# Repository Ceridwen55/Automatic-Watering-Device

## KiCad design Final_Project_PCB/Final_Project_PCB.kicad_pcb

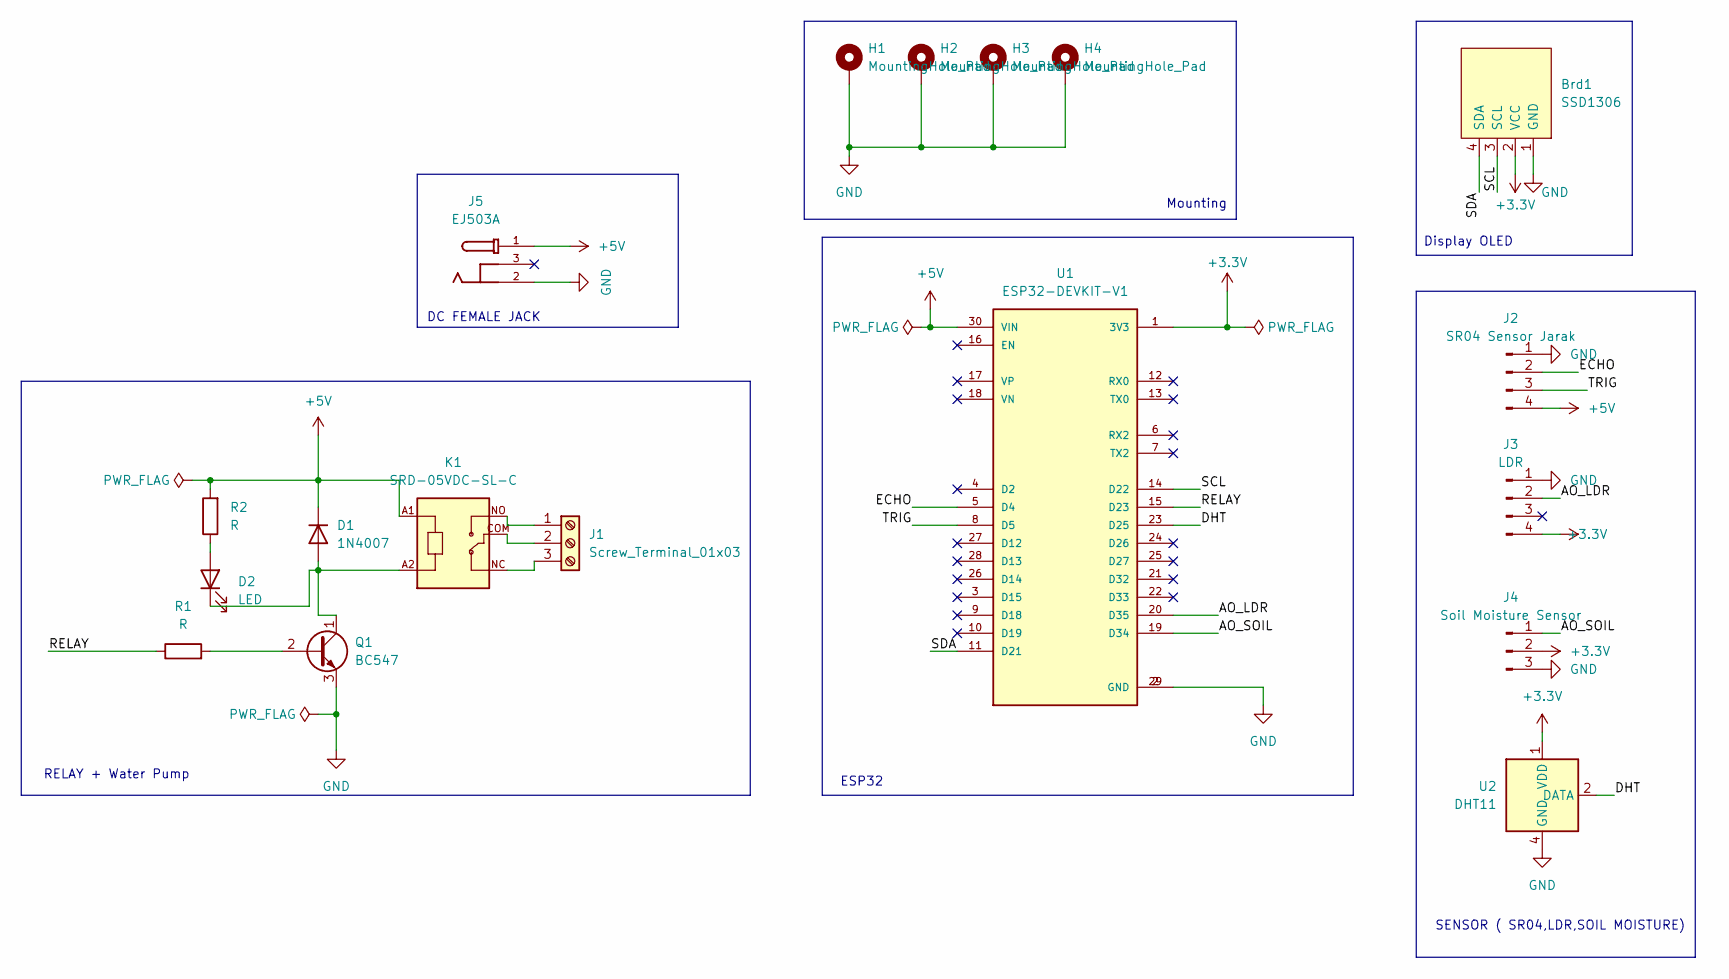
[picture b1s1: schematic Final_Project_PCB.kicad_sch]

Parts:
Brd1: SSD1306; 128x64OLED
D1: 1N4007; D_DO-41_SOD81_P10.16mm_Horizontal
D2: LED; LED_D3.0mm
H1, H2, H3, H4: MountingHole_Pad; MountingHole_3.2mm_M3_ISO14580_Pad
J1: Screw_Terminal_01x03; TerminalBlock_Phoenix_MKDS-1,5-3-5.08_1x03_P5.08mm_Horizont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
J2: SR04 Sensor Jarak; PinHeader_1x04_P2.54mm_Vertical
J3: LDR; PinHeader_1x04_P2.54mm_Vertical
J4: Soil Moisture Sensor; PinHeader_1x03_P2.54mm_Vertical
J5: EJ503A; MPD_EJ503A; PARTREV B
K1: SRD-05VDC-SL-C; RELAY_SRD-05VDC-SL-C
Q1: BC547; TO-92_Inline
R1, R2: R; R_Axial_DIN0207_L6.3mm_D2.5mm_P10.16mm_Horizontal
U1: ESP32-DEVKIT-V1; MODULE_ESP32_DEVKIT_V1; PARTREV N/A
U2: DHT11; Aosong_DHT11_5.5x12.0_P2.54mm

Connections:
+3.3V: Brd1.2 (VCC), J3.4, J4.2, U1.1 (3V3), U2.1 (VDD)
+5V: D1.1 (K), J2.4, J5.1, K1.A1, R2.2, U1.30 (VIN)
/AO_LDR: J3.2, U1.20 (D35)
/AO_SOIL: J4.1, U1.19 (D34)
/DHT: U1.23 (D25), U2.2 (DATA)
/ECHO: J2.2, U1.5 (D4)
/RELAY: R1.1, U1.15 (D23)
/SCL: Brd1.3 (SCL), U1.14 (D22)
/SDA: Brd1.4 (SDA), U1.11 (D21)
/TRIG: J2.3, U1.8 (D5)
GND: Brd1.1 (GND), H1.1, H2.1, H3.1, H4.1, J2.1, J3.1, J4.3, J5.2, Q1.3 (E), U1.2 (GND), U1.29 (GND), U2.4 (GND)
unnamed: D1.2 (A), D2.1 (K), K1.A2, Q1.1 (C)
unnamed: D2.2 (A), R2.1
unnamed: J1.1, K1.NO
unnamed: J1.2, K1.COM
unnamed: J1.3, K1.NC
unnamed: Q1.2 (B), R1.2

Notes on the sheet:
SENSOR ( SR04,LDR,SOIL MOISTURE)
Display OLED
Mounting
DC FEMALE JACK
RELAY + Water Pump
ESP32

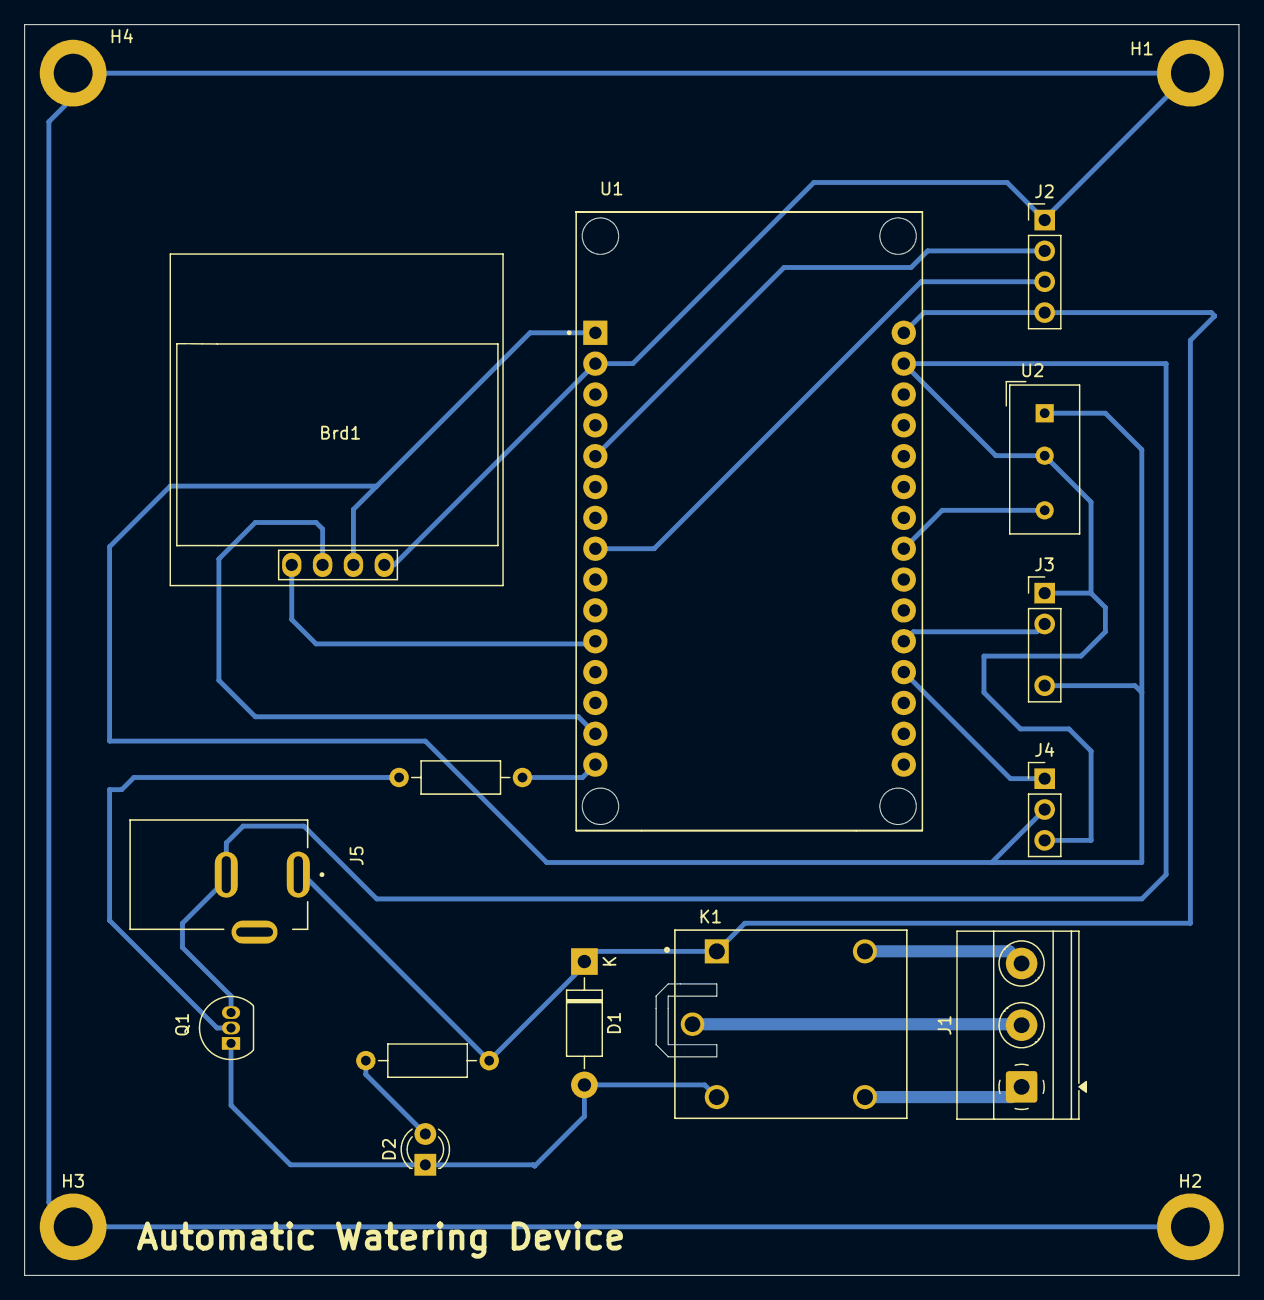
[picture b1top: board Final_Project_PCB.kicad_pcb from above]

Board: 2 copper layers, 100.0 x 103.0 mm, 18 parts (0 on the bottom side), 17 nets.

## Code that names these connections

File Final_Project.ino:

//PLAN
  // Bikin alat untuk deteksi suhu + humidity, kelembapan tanah, jarak, pompa DC, 
      // Intinya ada sensor sensor tertentu disetel ke I/O di ESP32
      // Konsep kerja alatnya:
          // Ketika suhu, kelembapan tanah, kelembapan udara, tinggi air sesuai, alat bakal nyemprotin Air ke tanaman
          // Tinggi air diukur dari sensor SR04
          // Kelembapan diukur dari sensor soil moisture (tancepin ke pot)
          // Udara tetap diukur pake DHT
          // Air bakal disedot dari container air pake pompa DC, terus nyiram ke tanaman jika Humidity, suhu, dan lainnya                   terpenuhi kondisinya
          // Kubikasi airnya bakal kita itung pake rumus pertanian pastinya per sedot nya
          // Sumber tenaga pakai baterai 
          // Semuanya dihubungin ke OLED buat display jadi tau data nya si user
      // Urutan kerja:
          // Alat ready
            // Ketika hasil sensor soil moisture mencapai angka < 40%, siram sampai 50% soil moisture
            // Ketika hasil sensor air humidity mencapai angka < 40%, siram sampai 50% soil moisture
            // Ketika hasil sensor suhu 24 derajat celcius dan lux 10.000-20.000 , siram sampai 60% soil moisture, stop jika >                60% soil moisture
            // Pas nyiram, buzzer idupin ( optional )
            

      
  // Bikin software nya satu satu dulu
  // Sambil bikin software, coba diatur desain HW nya di kicad
  // Pikirin konek ke HTTP, terus sambungin ke mobile Apps
  // "to be continued"

//DESIGN PROJECT
    // HARDWARE ( PCB Perfboard aja biar mudah dan ga ruwet)
    // PIN Data OLED (D22 (SCL), D21 (SDA))
    // PIN Data DHT  (D15)
    // PIN Data SR04 (D23, D19)
    // PIN Data LDR ( AO di D33 )
    // PIN Data Soil Moisture ( )
    // PIN Data Pompa DC ( ) 


    // SOFTWARE
    // Fungsi DHT
    // Fungsi SR04
    // Fungsi LDR
    // Fungsi Soil Moisture
    // Fungsi Pompa DC
    // Fungsi OLED
    




// HEADER

  //Header Arduino
  #include <Arduino.h>
  
  //Header Lib OLED
  #include <Wire.h>
  #include <Adafruit_GFX.h>
  #include <Adafruit_SSD1306.h>

  //Header Lib DHT (Adafruit)
  #include <DHT.h>
  #include <DHT_U.h>

  //Header Wifi
  #include <WiFi.h>
  #include <WiFiClientSecure.h>
  #include <HTTPClient.h>
  

//GLOBAL VAR

  //DHT
  #define PINDHT 15
  #define TipeDHT 22
  DHT Dht(PINDHT, TipeDHT);

  //LDR
  #define LDRPIN 33

  //SR04
  #define TRIG_PIN 19
  #define ECHO_PIN 23

  //OLED
  #define SCREEN_WIDTH 128 //OLED display width, in pixels
  #define SCREEN_HEIGHT 64 //OLED display height, in pixels
  Adafruit_SSD1306 display(SCREEN_WIDTH, SCREEN_HEIGHT, &Wire, -1);

  //Soil Moisture Sensor
  #define SOIL_PIN 32 //pin soil moisture Analog

  //RELAY Untuk DC PUMP
  #define PIN_RELAY 14

  //Parameter WiFi
  String ssid = "rumahjonan";
  String password = "halobocah12345";

  //Parameter URL
  String accessTokenDHT = "nxOYoRu12WrdzE4RHeFN";
  String urlDHT = "https://demo.thingsboard.io/api/v1/" + accessTokenDHT + "/telemetry";

  String accessTokenSoil = "q07s30i5nkosbivue8hm";
  String urlSoil = "https://demo.thingsboard.io/api/v1/" + accessTokenSoil + "/telemetry";

  String accessTokenLDR = "2LXxtQwe3cgEU1cPifVX";
  String urlLDR = "https://demo.thingsboard.io/api/v1/" + accessTokenLDR + "/telemetry";

  String accessTokenSR04 = "LZe6HEYrVTwmLXYHFJra";
  String urlSR04 = "https://demo.thingsboard.io/api/v1/" + accessTokenSR04 + "/telemetry";

void setup() {
  Serial.begin(9600);
  pinMode(TRIG_PIN, OUTPUT); // Init Trig SR04
  pinMode(ECHO_PIN, INPUT); // Init Echi SR04
  pinMode(PIN_RELAY, OUTPUT); //init pin relay
  Dht.begin(); //Init DHT
  WiFi.mode(WIFI_STA); // Mode Wifi 
  WiFi.begin(ssid,password); // Init Wifi
  
  display.begin();
  if(!display.begin(SSD1306_SWITCHCAPVCC, 0x3C)) //kalau ga begin, print
  {
    Serial.println(F("SSD1306 allocation failed"));
    for(;;);  // Jika OLED ga jalan, stop
  }

   display.clearDisplay();
   display.display();
}



void loop() 
{
  OLEDdanMekanisme();
  DataToThingsboard();
}

// LIST FUNGSI ALAT

float SR04()
{
  digitalWrite(TRIG_PIN, LOW);
  delayMicroseconds(2);
  digitalWrite(TRIG_PIN, HIGH);
  delayMicroseconds(10);
  digitalWrite(TRIG_PIN, LOW);

 
  long duration = pulseIn(ECHO_PIN, HIGH); // Baca durasi pulsa dari ECHO_PIN
  float distance = duration * 0.034 / 2; // Hitung jarak dalam cm
  delay(500);
  return distance;
  
}

float LDR()
{
  int ADCVal = analogRead(LDRPIN); // Baca nilai ADC dari pin LDR
  const float GAMMA = 0.7; // Konstanta Gamma untuk perhitungan lux
  const float RL10 = 33; // Resistansi LDR pada 10 lux (dalam kilo-ohm)

  // Perhitungan voltage
  float voltage = ADCVal / 4096.0 * 3.3;

  // Perhitungan resistansi LDR
  float resistance = 2000 * voltage / (1 - voltage / 3.3);

  // Perhitungan nilai lux
  float luxValue = pow(RL10 * 1e3 * pow(10, GAMMA) / resistance, (1 / GAMMA));
  
  delay(500);
  return luxValue;

  
}


void SoilMoisture ()
{
  int Soil = analogRead(SOIL_PIN);
  delay(100);
  return Soil;
}




void OLEDdanMekanisme()
{ 
 
  float luxValue = LDR();  // Alias LDR
  float distance = SR04(); // Alias SR04
  float soil = SoilMoisture(); // Alias Soil Moisture Sensor
  
  display.clearDisplay();
  display.setTextSize(1);
  display.setTextColor(WHITE);
  display.setCursor(0, 0);

  display.print("Cahaya: ");
  display.print(luxValue);
  display.println("lux");

  display.print("Jarak: ");
  display.print(distance); //print jarak dari SR04
  display.println(" cm");

  float degree = Dht.readTemperature(); // baca suhu
  float humidity = Dht.readHumidity(); // baca kelembapan

  display.print("Suhu: ");
  display.print(degree); // print suhu dari DHT
  display.println(" C");

  display.print("Kelembapan Udara: ");
  display.print(humidity); //print kelembapan dari DHT
  display.println(" %");

  display.print("Kelembapan Tanah: ");
  display.print(soil);
  display.println("%");


  display.display();

  if ((luxValue >= 10000) && (luxValue <= 20000) && (degree >=24) && (degree <= 27)) // Pastikan pagi hari, suhu dan intensitas cahaya terpenuhi pompa nyala
  {
    digitalWrite(PIN_RELAY,HIGH);
    if((soil >= 60) && (humidity >= 60)) // Jika humidity > 60%, berhenti
    {
      digitalWrite(PIN_RELAY,LOW);
    }
  }
  
}

void DataToThingsboard()
{
  WiFiClientSecure *clientDHT = new WiFiClientSecure; //DHT
  WiFiClientSecure *clientSoil = new WiFiClientSecure; //Soil
  WiFiClientSecure *clientLDR = new WiFiClientSecure; //LDR
  WiFiClientSecure *clientSR04 = new WiFiClientSecure; //SR04

  if(clientDHT)
  {
      float degree = Dht.readTemperature(); // baca suhu
      float humidity = Dht.readHumidity(); // baca kelembapan
  }

  if(clientSoil)
  {
    SoilMoisture();
  }

  if(clientLDR)
  {
    LDR();
  }

  if(clientSR04)
  {
    SR04();
  }


  clientDHT -> setInsecure();
  clientSoil -> setInsecure();
  clientLDR -> setInsecure();
  clientSR04 -> setInsecure();

  HTTPClient httpsDHT;
  HTTPClient httpsSoil;
  HTTPClient httpsLDR;
  HTTPClient httpsSR04;

  httpsDHT.begin(*clientDHT, urlDHT);
  httpsSoil.begin(*clientSoil, urlSoil);
  httpsLDR.begin(*clientLDR, urlLDR);
  httpsSR04.begin(*clientSR04, urlSR04);

  String payloadDHT = "{\"temperature\":" + String(degree) + ",\"humidity\":" + String(humidity) + "}";
  String payloadSoil = "{\"soilMoisture\":" + String(clientSoil) + "}";
  String payloadLDR = "{\"lux\":" + String(clientLDR) + "}";
  String payloadSR04 = "{\"distance\":" + String(clientSR04) + "}";

  int httpResponseCodeDHT = httpsDHT.POST(payloadDHT);
  int httpResponseCodeSoil = httpsSoil.POST(payloadSoil);
  int httpResponseCodeLDR = httpsLDR.POST(payloadLDR);
  int httpResponseCodeSR04 = httpsSR04.POST(payloadSR04);

  httpResponseCodeDHT.end();
  httpResponseCodeSoil.end();
  httpResponseCodeLDR.end();
  httpResponseCodeSR04.end():

  delay(10000);


}

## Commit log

2025-04-06 Commit 2
2025-04-07 Adding MQTT details
2025-04-07 Setting Pass MQTT
2025-04-07 Json Setup and other code fixes
2025-04-08 A little bit edit on code and adding PCB Design
2025-04-08 Adding edge cuts around Relay
2025-04-08 adding ground layer
2025-04-08 Adding gerber files
2025-04-12 Fixing Soil Moisture Formula
2025-04-12 Fixing Soil Moisture (2)
2025-04-15 Change IP to Localhost
2025-04-15 Adding Barrel Jack for 5v Source
2025-04-18 Adding 5v Source
2025-04-25 Turn PCB to single layer and create a new gerber file
2025-08-07 Doing some revision on PCB and tidying up code
